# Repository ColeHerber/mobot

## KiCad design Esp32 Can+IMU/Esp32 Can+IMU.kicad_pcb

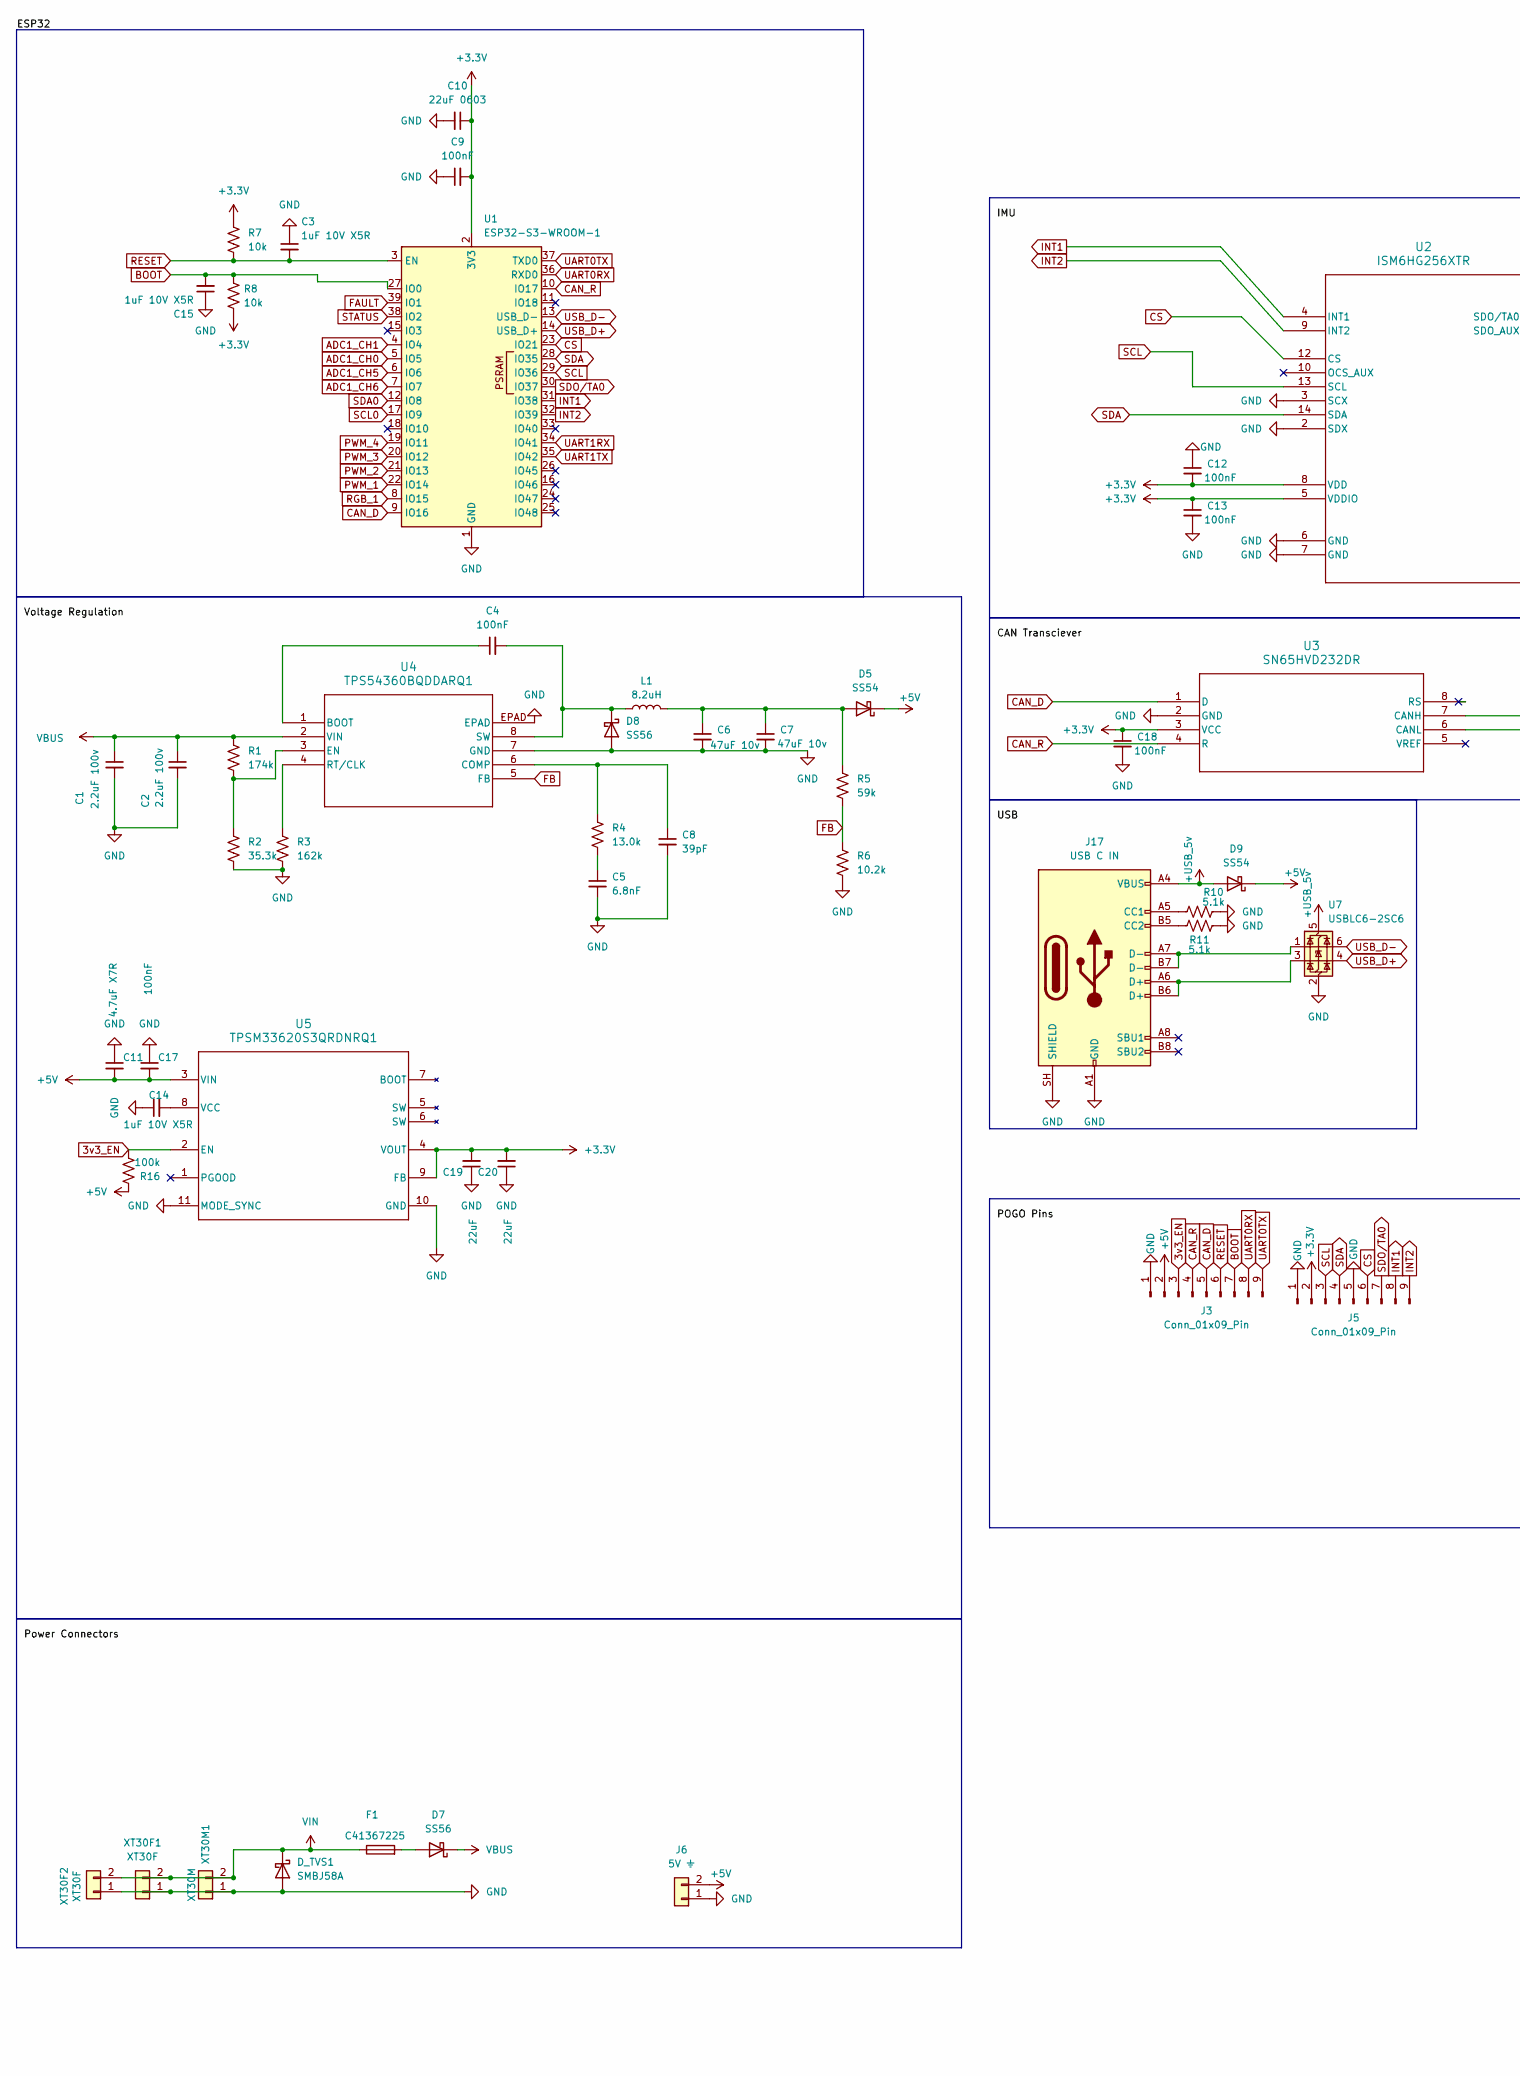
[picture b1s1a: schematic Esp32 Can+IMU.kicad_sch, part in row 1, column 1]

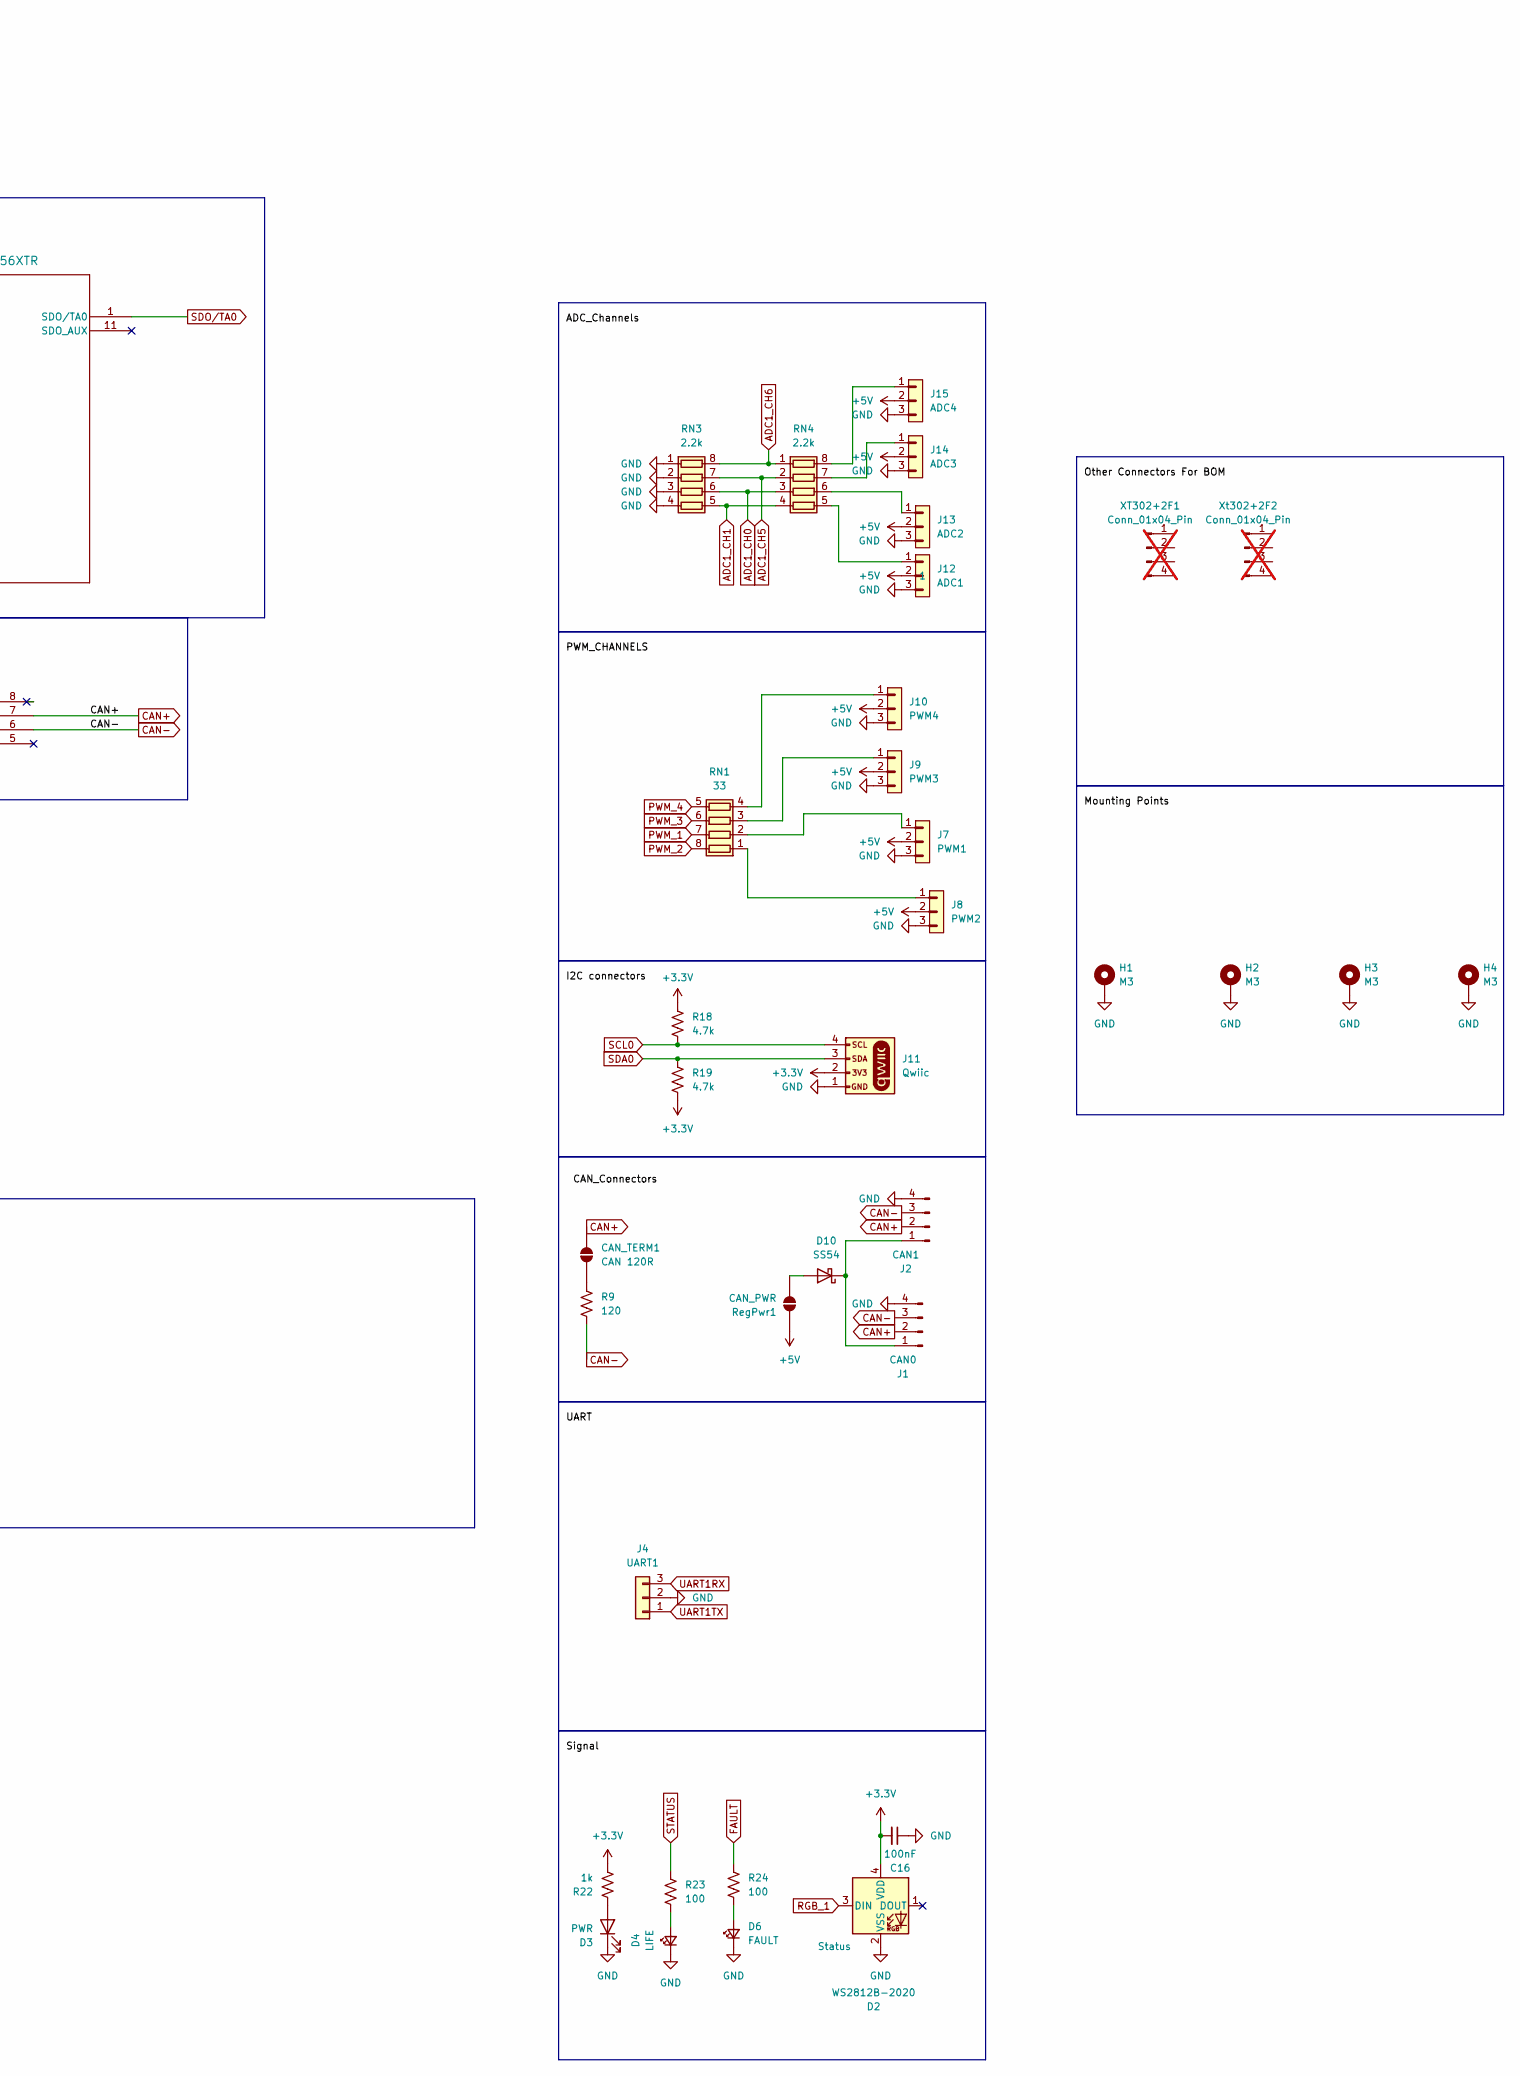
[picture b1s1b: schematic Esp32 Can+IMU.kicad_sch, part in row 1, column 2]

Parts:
C1, C2: 2.2uF 100v; C_1206_3216Metric
C3, C14, C15: 1uF 10V X5R; C_0402_1005Metric
C4, C9, C12, C13, C16, C17, C18: 100nF; C_0402_1005Metric
C5: 6.8nF; C_0402_1005Metric
C6, C7: 47uF 10v; C_1206_3216Metric
C8: 39pF; C_0402_1005Metric
C10: 22uF 0603; C_0603_1608Metric
C11: 4.7uF X7R; C_0805_2012Metric
C19, C20: 22uF; C_0805_2012Metric
CAN_TERM1: CAN 120R; SolderJumper-2_P1.3mm_Open_RoundedPad1.0x1.5mm
D2: WS2812B-2020; LED_WS2812B-2020_PLCC4_2.0x2.0mm
D3: PWR; LED_0603_1608Metric; LCSC# C2986048
D4: LIFE; LED_0603_1608Metric; LCSC# C19171390
D5, D9, D10: SS54; D_SMA
D6: FAULT; LED_0603_1608Metric; LCSC# C19171390
D7, D8: SS56; D_SMA
D_TVS1: SMBJ58A; D_SMB
F1: C41367225; Fuse_1206_3216Metric_Pad1.42x1.75mm_HandSolder; LCSC# C41367225
H1, H2, H3, H4: M3; MountingHole_3.2mm_M3_Pad_Via
J1: CAN0; JST_GH_SM04B-GHS-TB_1x04-1MP_P1.25mm_Horizontal; LCSC# C189895
J2: CAN1; JST_GH_SM04B-GHS-TB_1x04-1MP_P1.25mm_Horizontal; LCSC# C189895
J3, J5: Conn_01x09_Pin; Untitled
J4: UART1; JST_GH_SM03B-GHS-TB_1x03-1MP_P1.25mm_Horizontal
J6: 5V ⏚; PinHeader_1x02_P2.54mm_Vertical
J7: PWM1; PinHeader_1x03_P2.54mm_Vertical_Close
J8: PWM2; PinHeader_1x03_P2.54mm_Vertical_Close
J9: PWM3; PinHeader_1x03_P2.54mm_Vertical_Close
J10: PWM4; PinHeader_1x03_P2.54mm_Vertical_Close
J11: Qwiic; JST_SH_BM04B-SRSS-TB_1x04-1MP_P1.00mm_Vertical; LCSC# C160390
J12: ADC1; PinHeader_1x03_P2.54mm_Vertical_Close
J13: ADC2; PinHeader_1x03_P2.54mm_Vertical_Close
J14: ADC3; PinHeader_1x03_P2.54mm_Vertical_Close
J15: ADC4; PinHeader_1x03_P2.54mm_Vertical_Close
J17: USB C IN; USB_C_Receptacle_JAE_DX07S016JA1R1500
L1: 8.2uH; L_Changjiang_FNR4010S; LCSC# C45958745
R1: 174k; R_0603_1608Metric
R2: 35.3k; R_0402_1005Metric
R3: 162k; R_0402_1005Metric
R4: 13.0k; R_0402_1005Metric
R5: 59k; R_0402_1005Metric
R6: 10.2k; R_0402_1005Metric
R7, R8: 10k; R_0402_1005Metric
R9: 120; R_0402_1005Metric
R10, R11: 5.1k; R_0402_1005Metric
R16: 100k; R_0402_1005Metric
R18, R19: 4.7k; R_0402_1005Metric
R22: 1k; R_0402_1005Metric
R23, R24: 100; R_0402_1005Metric
RN1: 33; R_Array_Concave_4x0402
RN3, RN4: 2.2k; R_Array_Concave_4x0402
RegPwr1: CAN_PWR; SolderJumper-2_P1.3mm_Open_RoundedPad1.0x1.5mm
U1: ESP32-S3-WROOM-1; LCSC# C2913198
U2: ISM6HG256XTR; LGA14L_2P5X3_STM; LCSC# C51931514
U3: SN65HVD232DR; D8-L; LCSC# C30530
U4: TPS54360BQDDARQ1; DDA8_3P1X2P4_TEX-L; LCSC# C2687968
U5: TPSM33620S3QRDNRQ1; RDN0011B-MFG
U7: USBLC6-2SC6; SOT-23-6_Handsoldering
XT30F1, XT30F2: XT30F; AMASS_XT30UPB-F_1x02_P5.0mm_Vertical; LCSC# C108769
XT30M1: XT30M; AMASS_XT30UPB-M_1x02_P5.0mm_Vertical; LCSC# C19268026
XT302+2F1: Conn_01x04_Pin; LCSC# C19268028; not fitted
Xt302+2F2: Conn_01x04_Pin; LCSC# C19268028; not fitted

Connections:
3v3_EN: J3.3, R16.2, U5.2 (EN)
+3.3V: C9.2, C10.1, C12.2, C13.1, C16.2, C18.1, C19.2, C20.2, D2.4 (VDD), J5.2, J11.2, R7.1, R8.2, R18.1, R19.2, R22.2, U1.2 (3V3), U2.5 (VDDIO), U2.8 (VDD), U3.3 (VCC), U5.4 (VOUT), U5.9 (FB)
+5V: C11.2, C17.2, D5.1 (K), D9.1 (K), J3.2, J6.2, J7.2, J8.2, J9.2, J10.2, J12.2, J13.2, J14.2, J15.2, R16.1, RegPwr1.1 (A), U5.3 (VIN)
+USB_5v: D9.2 (A), J17.A4 (VBUS), J17.A9 (VBUS), J17.B4 (VBUS), J17.B9 (VBUS), U7.5 (VBUS)
ADC1_CH0: RN3.6 (R3.2), RN4.3 (R3.1), U1.5 (IO5)
ADC1_CH1: RN3.5 (R4.2), RN4.4 (R4.1), U1.4 (IO4)
ADC1_CH5: RN3.7 (R2.2), RN4.2 (R2.1), U1.6 (IO6)
ADC1_CH6: RN3.8 (R1.2), RN4.1 (R1.1), U1.7 (IO7)
BOOT: C15.2, J3.7, R8.1, U1.27 (IO0)
CAN+: CAN_TERM1.2 (B), J1.2, J2.2, U3.7 (CANH)
CAN-: J1.3, J2.3, R9.2, U3.6 (CANL)
CAN_D: J3.5, U1.9 (IO16), U3.1 (D)
CAN_R: J3.4, U1.10 (IO17), U3.4 (R)
CS: J5.6, U1.23 (IO21), U2.12 (CS)
FAULT: R24.2, U1.39 (IO1)
FB: R5.2, R6.1, U4.5 (FB)
GND: C1.2, C2.2, C3.1, C5.2, C6.2, C7.2, C8.2, C9.1, C10.2, C11.1, C12.1, C13.2, C14.1, C15.1, C16.1, C17.1, C18.2, C19.1, C20.1, D2.2 (VSS), D3.1 (K), D4.1 (K), D6.1 (K), D8.2 (A), D_TVS1.2 (A), H1.1 (1_1), H2.1 (1_1), H3.1 (1_1), H4.1 (1_1), J1.4, J2.4, J3.1, J4.2, J5.1, J5.5, J6.1, J7.3, J8.3, J9.3, J10.3, J11.1, J12.3, J13.3, J14.3, J15.3, J17.A1 (GND), J17.A12 (GND), J17.B1 (GND), J17.B12 (GND), J17.SH (SHIELD), R2.2, R3.2, R6.2, R10.2, R11.2, RN3.1 (R1.1), RN3.2 (R2.1), RN3.3 (R3.1), RN3.4 (R4.1), U1.1 (GND), U1.40 (GND), U1.41 (GND), U2.2 (SDX), U2.3 (SCX), U2.6 (GND), U2.7 (GND), U3.2 (GND), U4.7 (GND), U4.EPAD, U5.10 (GND), U5.11 (MODE_SYNC), U7.2 (GND), XT30F1.1, XT30F2.1, XT30M1.1
INT1: J5.8, U1.31 (IO38), U2.4 (INT1)
INT2: J5.9, U1.32 (IO39), U2.9 (INT2)
unnamed: C5.1, R4.2
unnamed: CAN_TERM1.1 (A), R9.1
unnamed: D3.2 (A), R22.1
unnamed: D4.2 (A), R23.1
unnamed: C6.1, C7.1, D5.2 (A), L1.2, R5.1
unnamed: D6.2 (A), R24.1
unnamed: D7.2 (A), F1.2
unnamed: C4.2, D8.1 (K), L1.1, U4.8 (SW)
unnamed: D10.2 (A), RegPwr1.2 (B)
unnamed: D10.1 (K), J1.1, J2.1
unnamed: J17.A5 (CC1), R10.1
unnamed: J17.B5 (CC2), R11.1
unnamed: J17.A6 (D+), J17.B6 (D+), U7.3 (I/O2)
unnamed: J17.A7 (D-), J17.B7 (D-), U7.1 (I/O1)
unnamed: J8.1, RN1.1 (R1.1)
unnamed: J7.1, RN1.2 (R2.1)
unnamed: J9.1, RN1.3 (R3.1)
unnamed: J10.1, RN1.4 (R4.1)
unnamed: J15.1, RN4.8 (R1.2)
unnamed: J14.1, RN4.7 (R2.2)
unnamed: J13.1, RN4.6 (R3.2)
unnamed: J12.1, RN4.5 (R4.2)
unnamed: C4.1, U4.1 (BOOT)
unnamed: C8.1, R4.1, U4.6 (COMP)
unnamed: R1.2, R2.1, U4.3 (EN)
unnamed: R3.1, U4.4 (RT/CLK)
unnamed: C14.2, U5.8 (VCC)
PWM_1: RN1.7 (R2.2), U1.22 (IO14)
PWM_2: RN1.8 (R1.2), U1.21 (IO13)
PWM_3: RN1.6 (R3.2), U1.20 (IO12)
PWM_4: RN1.5 (R4.2), U1.19 (IO11)
RESET: C3.2, J3.6, R7.2, U1.3 (EN)
RGB_1: D2.3 (DIN), U1.8 (IO15)
SCL: J5.3, U1.29 (IO36), U2.13 (SCL)
SCL0: J11.4, R18.2, U1.17 (IO9)
SDA: J5.4, U1.28 (IO35), U2.14 (SDA)
SDA0: J11.3, R19.1, U1.12 (IO8)
SDO/TA0: J5.7, U1.30 (IO37), U2.1 (SDO/TA0)
STATUS: R23.2, U1.38 (IO2)
UART0RX: J3.8, U1.36 (RXD0)
UART0TX: J3.9, U1.37 (TXD0)
UART1RX: J4.3, U1.34 (IO41)
UART1TX: J4.1, U1.35 (IO42)
USB_D+: U1.14 (USB_D+), U7.4 (I/O2)
USB_D-: U1.13 (USB_D-), U7.6 (I/O1)
VBUS: C1.1, C2.1, D7.1 (K), R1.1, U4.2 (VIN)
VIN: D_TVS1.1 (K), F1.1, XT30F1.2, XT30F2.2, XT30M1.2

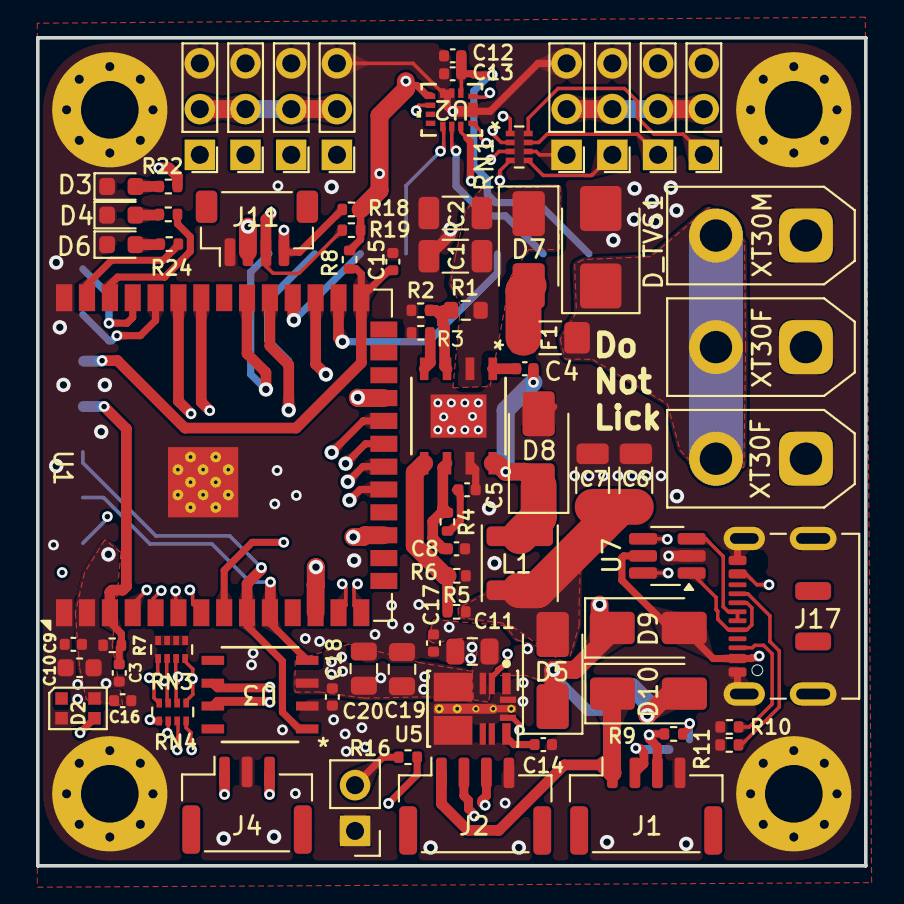
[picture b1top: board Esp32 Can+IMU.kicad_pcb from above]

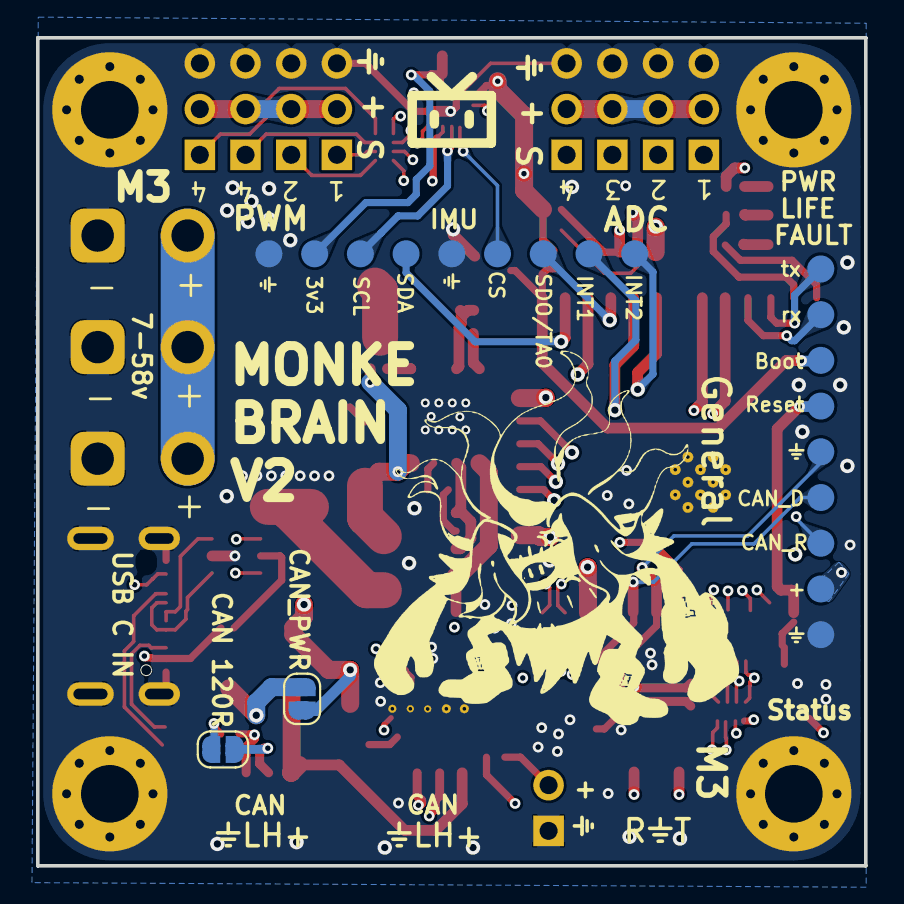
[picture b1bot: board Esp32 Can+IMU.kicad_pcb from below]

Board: 4 copper layers, 46.0 x 46.0 mm, 83 parts (3 on the bottom side), 66 nets.

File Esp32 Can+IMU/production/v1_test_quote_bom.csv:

Designator,Footprint,Quantity,Value,LCSC Part #
"C1, C2",1206,2,2.2uF 100v,
C10,0402,1,22uF,
C11,0402,1,1uF 10V X5R,
"C12, C13, C15, C3, C4, C9",0402,6,100nF,
C14,0402,1,4.7uF 10V X5R,
C5,0402,1,6.8nF,
"C6, C7",1206,2,47uF 10v,
C8,0402,1,39pF,
"D10, D5, D9",D_SMA,3,SS54,
D3,0603,1,PWR,
D4,0603,1,LIFE,
D6,0603,1,FAULT,
"D7, D8",D_SMA,2,SS56,
D_TVS1,D_SMB,1,SMBJ58A,
F1,1206,1,C41367225,
J1,JST_GH_SM04B-GHS-TB_1x04-1MP_P1.25mm_Horizontal,1,CAN0,
J11,JST_SH_BM04B-SRSS-TB_1x04-1MP_P1.00mm_Vertical,1,Qwiic,
J17,USB_C_Receptacle_JAE_DX07S016JA1R1500,1,USB C IN,
J2,JST_GH_SM04B-GHS-TB_1x04-1MP_P1.25mm_Horizontal,1,CAN1,
"J3, J5",Untitled,2,Conn_01x09_Pin,
J6,PinHeader_1x02_P2.54mm_Vertical,1,5V ⏚,
L1,L_Changjiang_FNR4010S,1,8.2uH,
R1,0402,1,174k,
"R10, R11",0402,2,5.1k,
"R12, R13, R14, R15",0402,4,33,
"R18, R19",0402,2,4.7k,
R2,0402,1,35.3k,
R22,0402,1,1k,
"R23, R24",0402,2,100Ω,
R3,0402,1,162k,
R4,0402,1,13.0k,
R5,0402,1,59k,
R6,0402,1,10.2k,
"R7, R8",0402,2,10k,
R9,0402,1,120,
U1,ESP32-S3-WROOM-1,1,ESP32-S3-WROOM-1,
U3,D8-L,1,SN65HVD230DR,
U4,DDA8_3P1X2P4_TEX-L,1,TPS54360BQDDARQ1,
U5,SOT-23-5,1,AP2112K-3.3,
U7,SOT-23-6_Handsoldering,1,USBLC6-2SC6,
"XT30F1, XT30F2",AMASS_XT30UPB-F_1x02_P5.0mm_Vertical,2,XT30F,
XT30M1,AMASS_XT30UPB-M_1x02_P5.0mm_Vertical,1,XT30M,

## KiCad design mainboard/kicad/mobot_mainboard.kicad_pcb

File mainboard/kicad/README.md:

# Mobot main board — KiCad 10 project

Open `mobot_mainboard.kicad_pro` in KiCad 10. Everything is on **one large sheet** (custom 1220 x 850 mm page),
grouped into titled blocks:

- Row 1 (power): Battery In / ESC Out, 5V regulator (TPS54360B), 3.3V regulator (TPSM33620S3), battery voltage sense / LED / flags, 4 GND mounting holes + rail test pads
- Row 2: ESP32-S3 + buttons, USB, status LEDs, S3 test pads, IMU island (supply, ISM6HG256X, SCH16T-K01, heater)
- Row 3: ESP32-P4 module (C6 unused), microSD, camera FPC + trigger, PWM headers, encoder Qwiic

Style follows the ESP32 CAN+IMU board: blue block boxes with titles and power symbols for +3.3V/+5V/GND.
Regulators, the heater, every decoupling cap and the microSD pull-ups are **drawn with wires**; global labels
are used only for connections between blocks (block inputs/outputs).

Project libraries: `mobot.kicad_sym` (SCH16T-K01, Waveshare ESP32-P4-Module) and `mobot.pretty`
(TPS54360B DDA8, TPSM33620 `TPSM33620_RDN0011B`, ISM6HG256X LGA14, SCH16T SOIC-24 *without* center pad,
Waveshare P4 module from Waveshare's DXF, G-Switch GT-TC048D-H025-L1 for RESET/BOOT; START is a 1x4 front-panel header, J4). STEP models in `3d/`.

`generator/` holds the scripts that produced it (`python3 -I generator/design.py <out_dir>`); they also report
estimated text/label overlaps. They overwrite the sheet, so **don't rerun them once the schematic has been edited by hand**.

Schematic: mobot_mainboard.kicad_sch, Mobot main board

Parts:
C1, C2, C6: 2.2uF 100V; C_1206_3216Metric
C3, C12, C16, C18, C20, C23, C27, C28, C29, C30, C32, C38: 100nF; C_0402_1005Metric
C4: 6.8nF; C_0402_1005Metric
C5: 39pF; C_0402_1005Metric
C7, C8: 47uF 10V; C_1206_3216Metric
C9: 4.7uF X7R; C_0805_2012Metric
C10, C19, C24, C26, C33, C34: 1uF; C_0402_1005Metric
C11: 4.7uF 25V; C_0805_2012Metric
C13, C17: 22uF; C_0603_1608Metric
C14, C15: 22uF; C_0805_2012Metric
C21, C22, C25, C31, C35, C37: 10uF; C_0805_2012Metric
C36: 100nF; C_0603_1608Metric_Pad1.08x0.95mm_HandSolder
C39, C40, C41, C42: 22uF 25V X5R; C_1210_3225Metric
C43: 100nF; C_0603_1608Metric_Pad1.08x0.95mm_HandSolder; not fitted
CAN0: CAN0; JST_GH_SM04B-GHS-TB_1x04-1MP_P1.25mm_Horizontal; not fitted
CAN1: CAN1; JST_GH_SM04B-GHS-TB_1x04-1MP_P1.25mm_Horizontal; not fitted
CAN_TERM: CAN 120R; SolderJumper-2_P1.3mm_Open_RoundedPad1.0x1.5mm; not fitted
D1: SMBJ12CA; D_SMB
D2, D3, D5, D6: SS54; D_SMA
D4: SS56; D_SMA
D7: PWR; LED_0603_1608Metric
D8: LIFE; LED_0603_1608Metric
D9: WS2812B-2020; LED_WS2812B-2020_PLCC4_2.0x2.0mm
FB1: 600R@100MHz; L_0603_1608Metric
H1, H2, H3, H4: GND; MountingHole_3.2mm_M3_Pad_Via
J1: BATT IN; AMASS_XT30UPB-F_1x02_P5.0mm_Vertical
J2: ESC OUT; AMASS_XT30UPB-M_1x02_P5.0mm_Vertical
J3: USB-C; USB_C_Receptacle_JAE_DX07S016JA1R1500
J4: START; PinHeader_1x04_P2.54mm_Vertical
J5: S3 UART; JST_GH_SM03B-GHS-TB_1x03-1MP_P1.25mm_Horizontal; not fitted
J6: microSD; microSD_HC_Hirose_DM3AT-SF-PEJM5
J7: P4 UART; JST_GH_SM03B-GHS-TB_1x03-1MP_P1.25mm_Horizontal; not fitted
J8: CAMERA; Molex_200528-0150_1x15-1MP_P1.00mm_Horizontal
J9: CAM TRIG; JST_SH_BM02B-SRSS-TB_1x02-1MP_P1.00mm_Vertical
J10: SERVO; PinHeader_3x04_P2.54mm_Servo
J11: ENCODER; JST_SH_BM04B-SRSS-TB_1x04-1MP_P1.00mm_Vertical
L1: 8.2uH; L_Changjiang_FNR4010S
Q1: AO3400A; SOT-23
R1: 174k; R_0603_1608Metric
R2: 43.2k; R_0402_1005Metric
R3: 162k; R_0402_1005Metric
R4: 13.0k; R_0402_1005Metric
R5: 59k; R_0402_1005Metric
R6: 10.2k; R_0402_1005Metric
R7, R21: 100k; R_0402_1005Metric
R8: 39k; R_0402_1005Metric
R9: 22k; R_0402_1005Metric
R10, R20, R32: 1k; R_0402_1005Metric
R11, R22, R23, R24, R25, R26, R27, R28, R29: 10k; R_0402_1005Metric
R12, R13: 5.1k; R_0402_1005Metric
R14: 100; R_0402_1005Metric
R15: 0R; R_0402_1005Metric
R16, R17, R18, R19: 39R 1W; R_2512_6332Metric; MPN RC2512FK-0739RL
R30, R31: 2.2k; R_0402_1005Metric
R33: 1.2k DNP; R_0402_1005Metric; not fitted
R34, R35: 4.7k; R_0402_1005Metric
R36: 120; R_0603_1608Metric_Pad0.98x0.95mm_HandSolder; not fitted
RN1: 22; R_Array_Concave_4x0402
RN2: 33; R_Array_Concave_4x0402
SW1: RESET; SW_GT-TC048D-H025-L1
SW2: BOOT; SW_GT-TC048D-H025-L1
TP1: VLOGIC; TestPoint_Pad_D1.0mm
TP2: 5V; TestPoint_Pad_D1.0mm
TP3: 3V3; TestPoint_Pad_D1.0mm
TP4: SYNC; TestPoint_Pad_D1.0mm
TP5: SCH SCK; TestPoint_Pad_D1.0mm
TP6: SCH MISO; TestPoint_Pad_D1.0mm
TP7: ISM SCK; TestPoint_Pad_D1.0mm
TP8: ISM MISO; TestPoint_Pad_D1.0mm
TP9: 3V3 IMU; TestPoint_Pad_D1.0mm
TP10: P4 D-; TestPoint_Pad_D1.0mm
TP11: P4 D+; TestPoint_Pad_D1.0mm
U1: TPS54360BQDDARQ1; DDA8_3P1X2P4_TEX-L
U2: TPSM33620S3QRDNRQ1; TPSM33620_RDN0011B
U3: ESP32-S3-WROOM-1-N8; ESP32-S3-WROOM-1
U4: USBLC6-2SC6 DNP; SOT-23-6; not fitted
U5: AP2112K-3.3; SOT-23-5
U6: SCH16T-K01-004; SCH16T_SOIC-24_Murata
U7: ISM6HG256XTR; LGA14L_2P5X3_STM
U8: ESP32-P4-Module; Waveshare_ESP32-P4-Module
U9: SN65HVD232DR; SOIC-8_3.9x4.9mm_P1.27mm; not fitted

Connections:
+3.3V: C13.1, C14.1, C15.1, C17.1, C18.1, C20.1, C31.1, C32.1, C35.1, C36.1, C37.1, C38.1, C43.1, D9.4 (VDD), J6.4 (VDD), J8.15, J11.2, R10.1, R11.1, R22.1, R23.1, R30.1, R31.1, R34.1, R35.1, TP3.1 (1_1), U2.4 (VOUT), U2.9 (FB), U3.2 (3V3), U8.84 (VBAT), U8.85 (ESP_3V3), U8.86 (ESP_3V3), U9.3 (VCC)
+3V3_IMU: C22.1, C23.1, C26.1, C27.1, C28.1, C29.1, C30.1, TP9.1 (1_1), U5.5 (VOUT), U6.8 (V3P3), U6.17 (V3P3), U6.18 (VDDIO), U7.5 (VDDIO), U7.8 (VDD)
+5V: D5.1 (K), D6.1 (K), FB1.1, R16.1, R17.1, R18.1, R19.1, TP2.1 (1_1)
CAM_PWR_EN: J8.11, U8.24 (GPIO9)
CAM_SCL: J8.13, R30.2, U8.22 (GPIO7)
CAM_SDA: J8.14, R31.2, U8.23 (GPIO8)
CAM_TRIG: J9.1, R32.2, R33.1
CAN+: CAN0.2, CAN1.2, CAN_TERM.2 (B), U9.7 (CANH)
CAN-: CAN0.3, CAN1.3, R36.1, U9.6 (CANL)
CAN_D: U3.9 (IO16), U9.1 (D)
CAN_R: U3.39 (IO1), U9.4 (R)
CAN_TERM: CAN_TERM.1 (A), R36.2
CSI_CLK_N: J8.8, U8.44 (CSI_CLKN)
CSI_CLK_P: J8.9, U8.43 (CSI_CLKP)
CSI_D0_N: J8.2, U8.41 (CSI_DATAN0)
CSI_D0_P: J8.3, U8.42 (CSI_DATAP0)
CSI_D1_N: J8.5, U8.45 (CSI_DATAN1)
CSI_D1_P: J8.6, U8.46 (CSI_DATAP1)
ENC_SCL: J11.4, R35.2, U3.17 (IO9)
ENC_SDA: J11.3, R34.2, U3.12 (IO8)
GND: C1.2, C2.2, C4.2, C5.2, C6.2, C7.2, C8.2, C9.2, C10.1, C11.2, C12.2, C13.2, C14.2, C15.2, C16.2, C17.2, C18.2, C19.2, C20.2, C21.2, C22.2, C23.2, C24.2, C25.2, C26.2, C27.2, C28.2, C29.2, C30.2, C31.2, C32.2, C33.2, C34.2, C35.2, C36.2, C37.2, C38.2, C39.2, C40.2, C41.2, C42.2, C43.2, CAN0.4, CAN1.4, D1.1 (A1), D4.2 (A), D7.1 (K), D8.1 (K), D9.2 (VSS), H1.1 (1_1), H2.1 (1_1), H3.1 (1_1), H4.1 (1_1), J1.1, J2.1, J3.A1 (GND), J3.A12 (GND), J3.B1 (GND), J3.B12 (GND), J3.SH (SHIELD), J4.2, J4.4, J5.1, J6.6 (VSS), J6.SH (SHIELD), J7.1, J8.1, J8.4, J8.7, J8.10, J9.2, J10.3 (ESC_GND), J10.6 (STEER_F_GND), J10.9 (STEER_R_GND), J10.12 (SPARE_GND), J11.1, Q1.2 (S), R2.2, R3.2, R6.2, R9.2, R12.2, R13.2, R21.2, R33.2, SW1.2, SW2.2, U1.7 (GND), U1.EPAD, U2.10 (GND), U2.11 (MODE_SYNC), U3.1 (GND), U3.40 (GND), U3.41 (GND), U4.2 (GND), U5.2 (GND), U6.1 (HEATSINK), U6.3 (TA9), U6.4 (TA8), U6.5 (RESERVED), U6.7 (RESERVED), U6.9 (GND), U6.12 (GND), U6.13 (GND), U6.16 (GND), U6.24 (HEATSINK), U7.2 (SDX), U7.3 (SCX), U7.6 (GND), U7.7 (GND), U8.1 (GND), U8.3 (GND), U8.15 (GND), U8.33 (GND), U8.40 (GND), U8.47 (GND), U8.52 (GND), U8.83 (GND), U9.2 (GND)
HEATER_PWM: R20.1, U3.33 (IO40)
ISM_CS: U3.23 (IO21), U7.12 (CS)
ISM_INT1: U3.31 (IO38), U7.4 (INT1)
ISM_INT2: U3.32 (IO39), U7.9 (INT2)
ISM_MISO: TP8.1 (1_1), U3.30 (IO37), U7.1 (SDO/TA0)
ISM_MOSI: RN1.5 (R4.2), U7.14 (SDA)
ISM_SCK: RN1.6 (R3.2), TP7.1 (1_1), U7.13 (SCL)
unnamed: C4.1, R4.2
unnamed: C3.2, D4.1 (K), L1.1, U1.8 (SW)
unnamed: C7.1, C8.1, C9.1, D5.2 (A), L1.2, R5.2
unnamed: D7.2 (A), R10.2
unnamed: D8.2 (A), R14.2
unnamed: Q1.3 (D), R16.2, R17.2, R18.2, R19.2
unnamed: Q1.1 (G), R20.2, R21.1
unnamed: C3.1, U1.1 (BOOT)
unnamed: C5.1, R4.1, U1.6 (COMP)
unnamed: R1.2, R2.1, U1.3 (EN)
unnamed: R5.1, R6.1, U1.5 (FB)
unnamed: R3.1, U1.4 (RT/CLK)
unnamed: R7.2, U2.2 (EN)
unnamed: C10.2, U2.8 (VCC)
unnamed: C21.1, FB1.2, U5.1 (VIN), U5.3 (EN)
unnamed: R15.1, U6.20 (DRY_SYNC)
unnamed: C25.1, U6.10 (VREGA2), U6.11 (VREGA)
unnamed: C24.1, U6.14 (VREGD2), U6.15 (VREGD)
P4_BOOT: U3.11 (IO18), U8.62 (GPIO35/BOOT)
P4_BOOT_EN: R23.2, U8.63 (GPIO36/BOOT_EN)
P4_EN: C33.1, R22.2, U3.15 (IO3), U8.87 (ESP_EN)
P4_TO_S3: J7.3, U3.34 (IO41), U8.64 (GPIO37/U0TXD)
P4_USBJ_DN: TP10.1 (1_1), U8.50 (GPIO24/USB_FS_DN)
P4_USBJ_DP: TP11.1 (1_1), U8.51 (GPIO25/USB_FS_DP)
P4_VO4: C34.1, R24.1, R25.2, R26.2, R27.1, R28.1, R29.2, U8.66 (ESP_LDO_VO4)
PWM_ESC: RN2.4 (R4.1), U3.19 (IO11)
PWM_SPARE: RN2.1 (R1.1), U3.22 (IO14)
PWM_STEER_F: RN2.3 (R3.1), U3.20 (IO12)
PWM_STEER_R: RN2.2 (R2.1), U3.21 (IO13)
RGB_DIN: D9.3 (DIN), U3.8 (IO15)
S3_BOOT: SW2.1, U3.27 (IO0)
S3_EN: C19.1, R11.2, SW1.1, U3.3 (EN)
S3_ISM_MOSI: RN1.4 (R4.1), U3.28 (IO35)
S3_ISM_SCK: RN1.3 (R3.1), U3.29 (IO36)
S3_SCH_MOSI: RN1.2 (R2.1), U3.6 (IO6)
S3_SCH_SCK: RN1.1 (R1.1), U3.5 (IO5)
S3_TO_P4: J7.2, U3.35 (IO42), U8.65 (GPIO38/U0RXD)
S3_U0RXD: J5.2, U3.36 (RXD0)
S3_U0TXD: J5.3, U3.37 (TXD0)
S3_USB_DN: J3.A7 (D-), J3.B7 (D-), U3.13 (USB_D-), U4.1 (I/O1), U4.6 (I/O1)
S3_USB_DP: J3.A6 (D+), J3.B6 (D+), U3.14 (USB_D+), U4.3 (I/O2), U4.4 (I/O2)
SCH_CS: U3.18 (IO10), U6.22 (CS)
SCH_EXTRESN: U3.24 (IO47), U6.6 (EXTRESN)
SCH_MISO: TP6.1 (1_1), U3.7 (IO7), U6.19 (MISO)
SCH_MOSI: RN1.7 (R2.2), U6.23 (MOSI)
SCH_SCK: RN1.8 (R1.2), TP5.1 (1_1), U6.21 (SCK)
SD_CLK: J6.5 (CLK), U8.71 (GPIO43*)
SD_CMD: J6.3 (CMD), R24.2, U8.72 (GPIO44*)
SD_D0: J6.7 (DAT0), R25.1, U8.67 (GPIO39*)
SD_D1: J6.8 (DAT1), R26.1, U8.68 (GPIO40*)
SD_D2: J6.1 (DAT2), R27.2, U8.69 (GPIO41*)
SD_D3: J6.2 (DAT3/CD), R28.2, U8.70 (GPIO42*)
SD_DET: J6.9 (DET), R29.1, U8.73 (GPIO45*)
SIG_ESC: J10.1 (ESC_SIG), RN2.5 (R4.2)
SIG_SPARE: J10.10 (SPARE_SIG), RN2.8 (R1.2)
SIG_STEER_F: J10.4 (STEER_F_SIG), RN2.6 (R3.2)
SIG_STEER_R: J10.7 (STEER_R_SIG), RN2.7 (R2.2)
START_BTN: J4.1, U3.16 (IO46)
START_LED: J4.3, U3.10 (IO17)
STATUS_LED: R14.1, U3.38 (IO2)
SYNC: R15.2, R32.1, TP4.1 (1_1), U3.25 (IO48), U8.17 (GPIO2)
USB_CC1: J3.A5 (CC1), R12.1
USB_CC2: J3.B5 (CC2), R13.1
USB_VBUS: D3.2 (A), D6.2 (A), J3.A4 (VBUS), J3.A9 (VBUS), J3.B4 (VBUS), J3.B9 (VBUS), U4.5 (VBUS)
VBAT: C1.1, C2.1, C6.1, C39.1, C40.1, C41.1, C42.1, D1.2 (A2), D2.2 (A), J1.2, J2.2, J10.5 (STEER_F_V+), J10.8 (STEER_R_V+), J10.11 (SPARE_V+), R1.1, R8.1, U1.2 (VIN)
VBAT_SENSE: C16.1, R8.2, R9.1, U3.4 (IO4)
VLOGIC: C11.1, C12.1, D2.1 (K), D3.1 (K), R7.1, TP1.1 (1_1), U2.3 (VIN)

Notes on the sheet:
AP2112K-3.3 (on hand): Vin <= 6 V, so it is fed from +5V, never VBAT.
4 x 39R in parallel = 9.75R -> 2.6 W at 5 V (0.64 W each, 2512 = 1 W). One per side of U6, bottom side.
Encoder (Qwiic)
ISM6HG256X (backup gyro, SPI2) - CAN-board circuit
Mobot main board - single-sheet schematic. Blocks connect through global labels (CAN+IMU board style);
C28 = C5 (VDDIO). Place each at its pin on the top layer, ESR < 100 mOhm. SPI mode 0, <= 10.5 MHz.
No hardware cutoff: R21 holds the heater off whenever the S3 is in reset or not driving HEATER_PWM.
Pi FPC: pin 11 = camera power enable, 12 unused. Trigger wire to the camera board XVS/FSIN pad.
Design decisions and open items: mainboard/PLAN.md
Status LEDs (LIFE heartbeat + NeoPixel for status/faults)
microSD (P4 SDMMC slot 0, 4-bit) - pull-ups to P4_VO4 at the socket
Heater (4 x 39R, one on each side of SCH16T)
ESP32-P4 Module (Waveshare: P4NRW32; on-module C6 unused)
VLOGIC 3-36 V. 3.3 V loads: P4 module (P4 + PSRAM + C6 Wi-Fi), S3, camera, encoder, LEDs.
Mounting Holes (GND, double as GND test points) / Rail Test Pads
IO45 unused (strapping). IO46 = START, IO17 = START LED, IO0 = BOOT (internal pull-ups).
ESP32
Firmware: watchdog on, duty cap, SCH16T vs ISM6HG256X temperature cross-check. HEATER_PWM >= 20 kHz or a few Hz.
regulators, heater and decoupling are drawn with wires. Power symbols: +3.3V, +5V, GND.
VLOGIC = diode-OR of VBAT and USB_VBUS -> 3.3 V regulator (S3 + P4 run from USB alone).
Island Supply (+5V -> ferrite -> AP2112K-3.3)
SD slot 0 IOMUX: CLK 43, CMD 44, D0-D3 39-42 (verify vs P4 TRM before layout).
Pull-ups go to P4_VO4 (the SD I/O domain), not +3.3V.
Boot: GPIO35 low at EN rise = download (GPIO36 pulled up). UART0 = GPIO37 TX / GPIO38 RX.
Camera: Arducam OV9281 NoIR M12 (Pi 15-pin 1.0 mm FPC, 2-lane)
XT30: 15 A cont / 30 A for 1 min. Confirm launch current (PLAN D8).
UVLO R1/R2: start ~5.8 V, stop ~5.2 V (CAN board R2 = 35.3k gave 6.9 / 6.3 V: too high for 2S).
VBAT_SENSE = VBAT x 0.361 (8.4 V -> 3.03 V), read directly from the battery input -> S3 IO4.
FB R5/R6 -> 5.43 V before D5; D5 drops it to ~5.0 V on +5V.
C6 co-processor unused (Wi-Fi comes from the S3): LNA_OUT open; firmware holds C6 in reset via GPIO54.
ESC current: J1 -> J2 only (short wide pours on L1+L4). No fuse on this board.
Caps per datasheet Table 80: C24 = C1 (VREGD), C25 = C2 (VREGA), C26 = C3 (V3P3 pin 17), C27 = C4 (V3P3 pin 8),
Test Pads (bare pads, no pogo)
+5V loads: heater (~0.5 A) + IMU LDO (~45 mA). Firmware: heater off when running from USB only.
Battery In / ESC Out
Voltage Regulation 3.3V (TPSM33620S3)
Do NOT use: GPIO6 (pad 21) + GPIO54 (pad 82) = C6 link; GPIO0/1 (pads 88/16) = 32 kHz xtal on module.
SCH16T-K01 (primary gyro, SafeSPI on SPI3)
J11 = AS5600 encoder (I2C0, 400 kHz, address 0x36).
USB (S3 native USB; also bridges P4 UART0 for flashing)

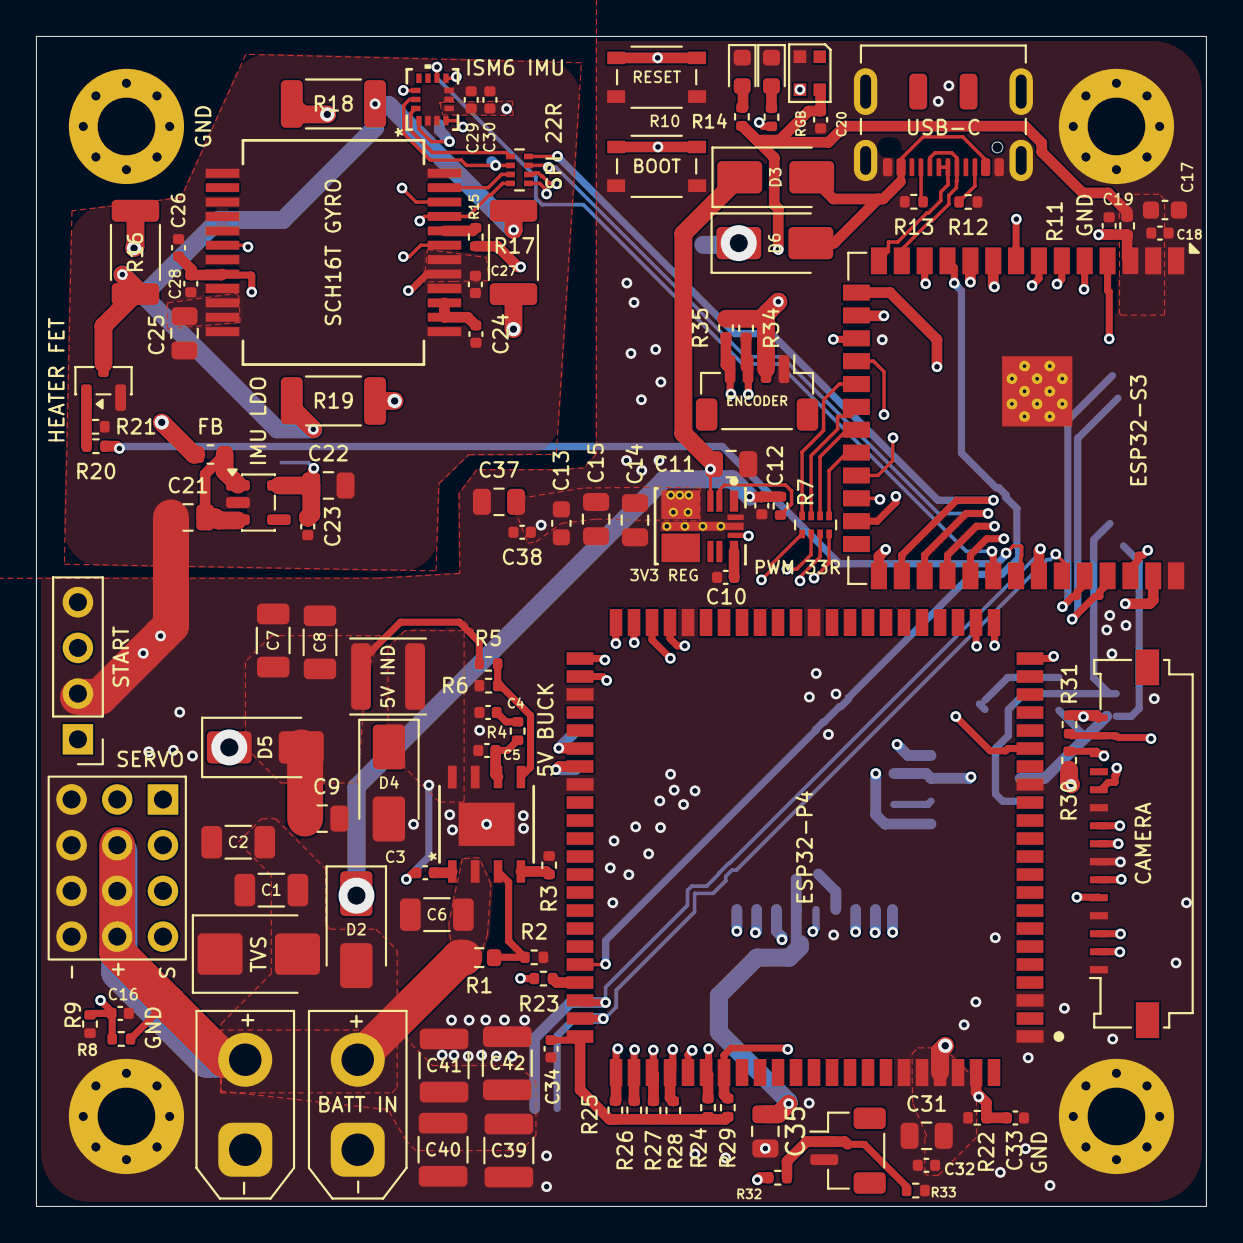
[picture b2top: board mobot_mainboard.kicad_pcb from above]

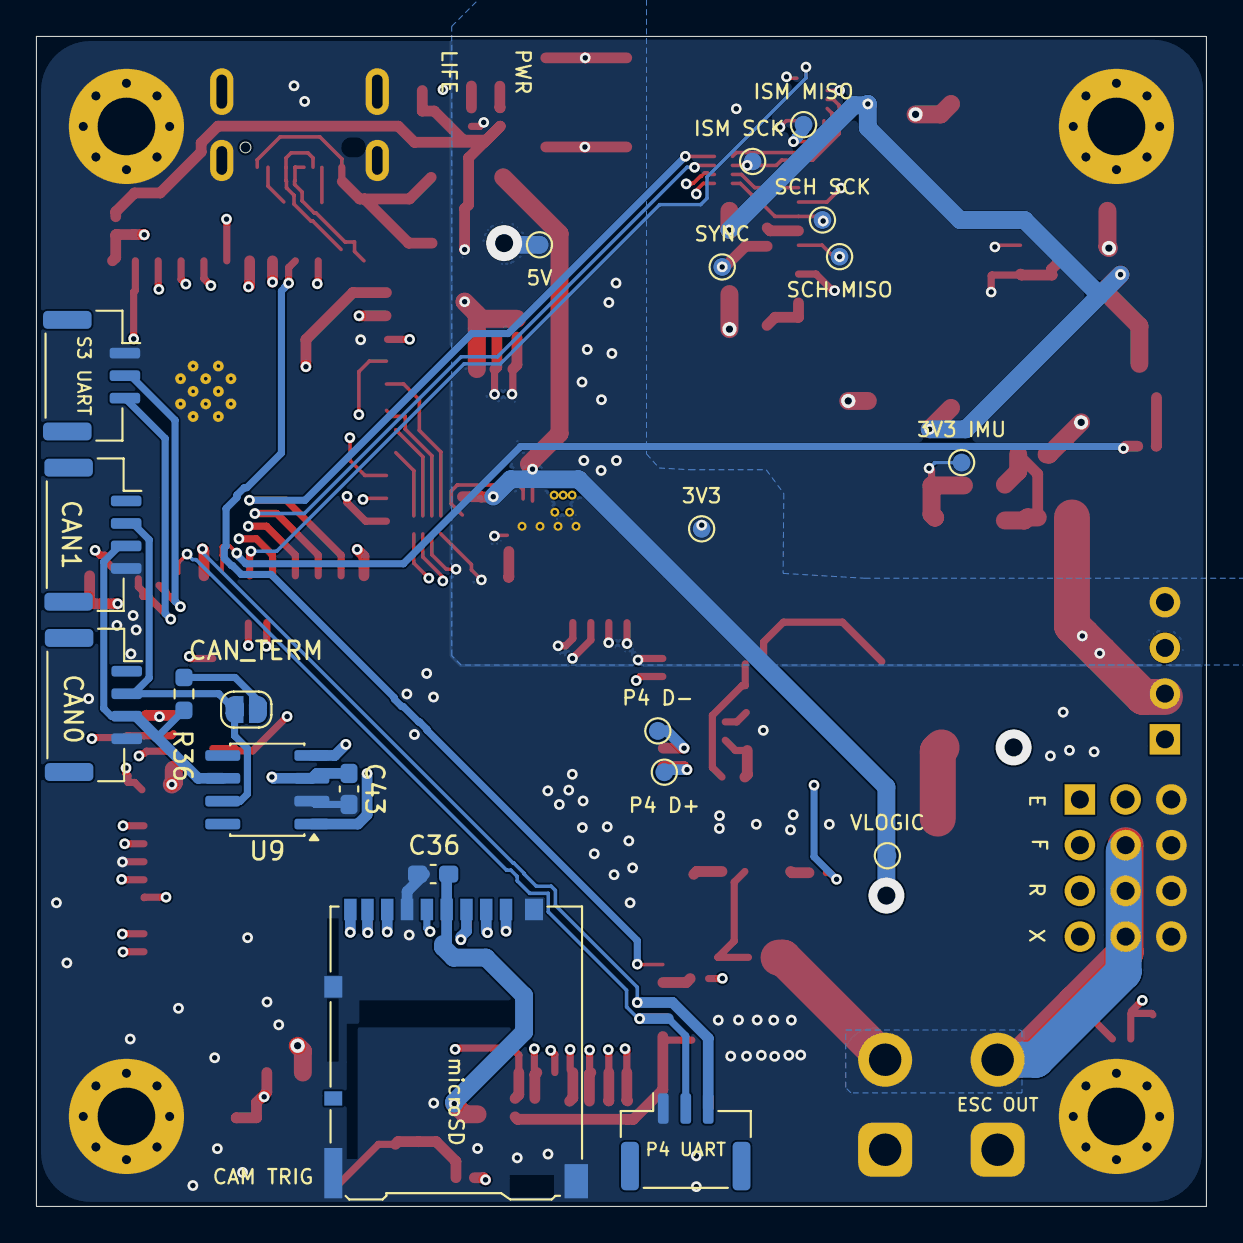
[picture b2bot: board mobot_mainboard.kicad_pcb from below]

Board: 4 copper layers, 65.0 x 65.0 mm, 132 parts (21 on the bottom side), 95 nets.
